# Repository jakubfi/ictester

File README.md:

# Logic IC Tester

Main goal of this project was to make a logic IC tester that allows adding new tests and support for new ICs easily.

## Features

* fully programmable (client-side, in python)
* designed for 5 V TTL logic, but other 5 V logic families can be tested too
* current limiting to 200mA
* current and voltage measurement on VCC and GND pins
* 1.7 μs (<=16-pin ICs) and 2.15 μs (>16-pin ICs) per single logic test cycle
* built-in tests for 4164 and 41256 memories (MARCH C- test in read+write, read/write and page access modes)
* built-in tests for 74121, 74122 and 74123 univibrators
* small and USB powered

## Components

Project is split into three parts:

* [controller](controller) - software for controlling the tester. Look there for command line usage.
* [firmware](fw) - IC tester firmware
* [hardware](hw) - KiCad project files (see also [this pdf](doc/ictester.pdf) for schematic)

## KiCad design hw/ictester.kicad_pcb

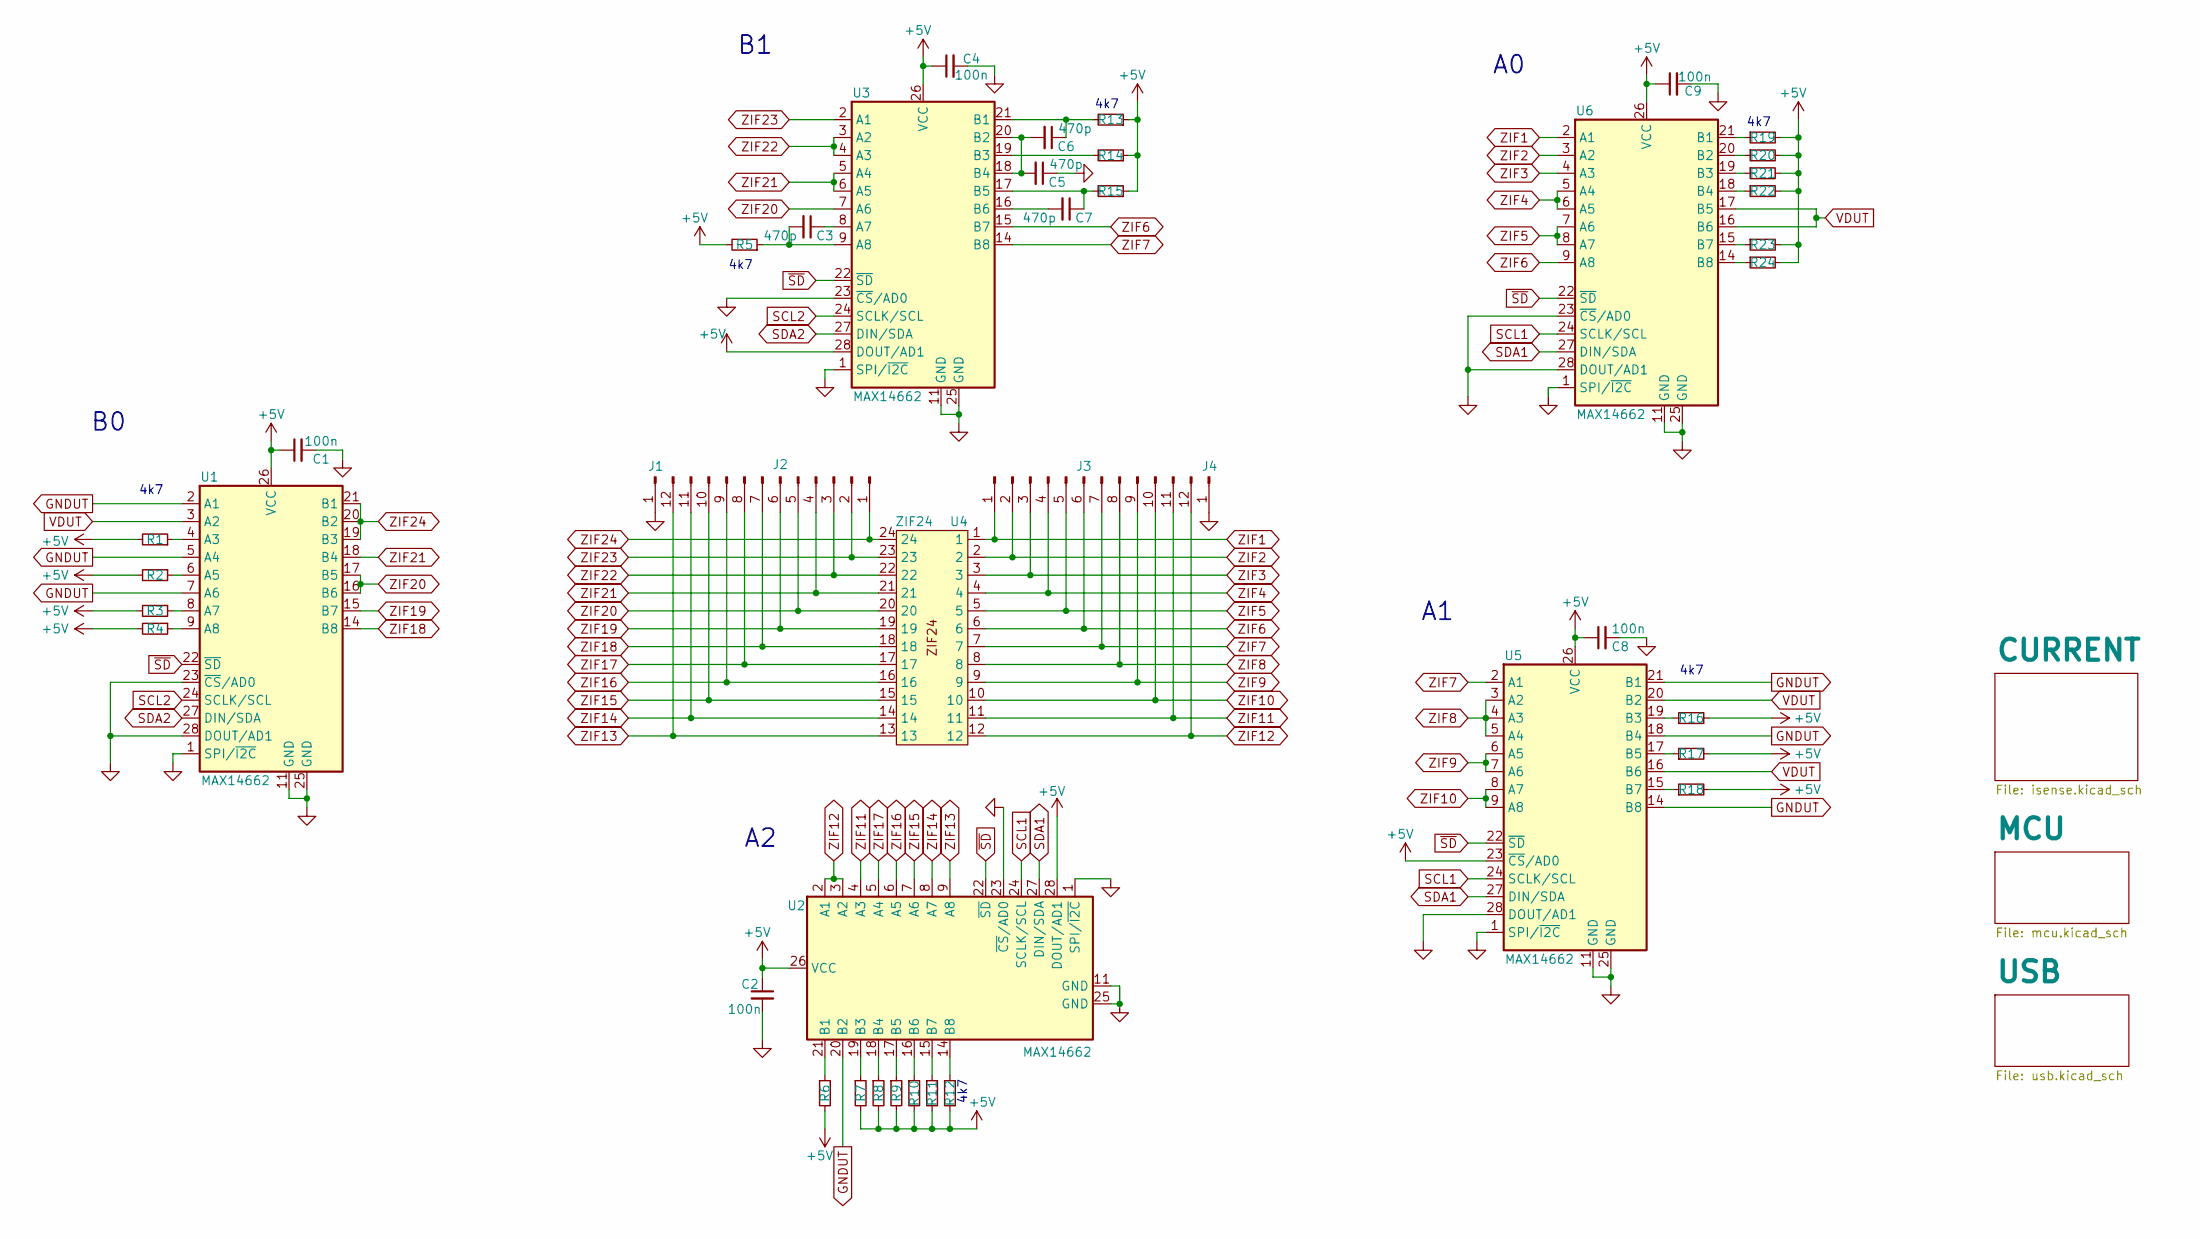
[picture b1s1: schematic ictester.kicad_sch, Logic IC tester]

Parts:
C1, C2, C4, C8, C9: 100n; C_0805_2012Metric_Pad1.18x1.45mm_HandSolder
C3, C5, C6, C7: 470p; C_0805_2012Metric_Pad1.18x1.45mm_HandSolder
J1, J4: Conn_01x01_Pin; PinHeader_1x01_P2.54mm_Vertical
J2, J3: Conn_01x12_Pin; PinHeader_1x12_P2.54mm_Vertical
R1, R2, R3, R4, R5, R6, R7, R8, R9, R10, R11, R12, R13, R14, R15, R16, R17, R18, R19, R20, R21, R22, R23, R24: 4k7; R_0805_2012Metric_Pad1.20x1.40mm_HandSolder
U1, U2, U3, U5, U6: MAX14662; QFN-28-1EP_4x4mm_P0.4mm_EP2.6x2.6mm
U4: ZIF24; DIP_Socket-24_W11.9_W12.7_W15.24_W17.78_W18.5_3M_224-1275-0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

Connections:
+5V: C1.1, C2.1, C4.1, C8.1, C9.1, R1.2, R2.2, R3.2, R4.2, R5.2, R6.2, R7.2, R8.2, R9.2, R10.2, R11.2, R12.2, R13.1, R14.1, R15.1, R16.2, R17.2, R18.2, R19.2, R20.2, R21.2, R22.2, R23.2, R24.2, U1.26 (VCC), U2.26 (VCC), U2.28 (DOUT/AD1), U3.26 (VCC), U3.28 (DOUT/AD1), U5.23 (~CS/AD0), U5.26 (VCC), U6.26 (VCC); also elsewhere on the board
GND: C1.2, C2.2, C4.2, C5.1, C8.2, C9.2, J1.1, J4.1, U1.1 (SPI/~I2C), U1.11 (GND), U1.23 (~CS/AD0), U1.25 (GND), U1.28 (DOUT/AD1), U1.29 (GND), U2.1 (SPI/~I2C), U2.11 (GND), U2.23 (~CS/AD0), U2.25 (GND), U2.29 (GND), U3.1 (SPI/~I2C), U3.11 (GND), U3.23 (~CS/AD0), U3.25 (GND), U3.29 (GND), U5.1 (SPI/~I2C), U5.11 (GND), U5.25 (GND), U5.28 (DOUT/AD1), U5.29 (GND), U6.1 (SPI/~I2C), U6.11 (GND), U6.23 (~CS/AD0), U6.25 (GND), U6.28 (DOUT/AD1), U6.29 (GND); also elsewhere on the board
GNDUT: U1.2 (A1), U1.5 (A4), U1.7 (A6), U2.20 (B2), U5.14 (B8), U5.18 (B4), U5.21 (B1); also elsewhere on the board
unnamed: R1.1, U1.4 (A3)
unnamed: R2.1, U1.6 (A5)
unnamed: R3.1, U1.8 (A7)
unnamed: R4.1, U1.9 (A8)
unnamed: R6.1, U2.21 (B1)
unnamed: R7.1, U2.19 (B3)
unnamed: R8.1, U2.18 (B4)
unnamed: R9.1, U2.17 (B5)
unnamed: R10.1, U2.16 (B6)
unnamed: R11.1, U2.15 (B7)
unnamed: R12.1, U2.14 (B8)
unnamed: C3.1, U3.8 (A7)
unnamed: C3.2, R5.1, U3.9 (A8)
unnamed: C6.1, R13.2, U3.21 (B1)
unnamed: C5.2, C6.2, U3.18 (B4), U3.20 (B2)
unnamed: R14.2, U3.19 (B3)
unnamed: C7.1, R15.2, U3.17 (B5)
unnamed: C7.2, U3.16 (B6)
unnamed: R16.1, U5.19 (B3)
unnamed: R17.1, U5.17 (B5)
unnamed: R18.1, U5.15 (B7)
unnamed: R19.1, U6.21 (B1)
unnamed: R20.1, U6.20 (B2)
unnamed: R21.1, U6.19 (B3)
unnamed: R22.1, U6.18 (B4)
unnamed: R23.1, U6.15 (B7)
unnamed: R24.1, U6.14 (B8)
SCL1: U2.24 (SCLK/SCL), U5.24 (SCLK/SCL), U6.24 (SCLK/SCL); also elsewhere on the board
SCL2: U1.24 (SCLK/SCL), U3.24 (SCLK/SCL); also elsewhere on the board
SDA1: U2.27 (DIN/SDA), U5.27 (DIN/SDA), U6.27 (DIN/SDA); also elsewhere on the board
SDA2: U1.27 (DIN/SDA), U3.27 (DIN/SDA); also elsewhere on the board
VDUT: U1.3 (A2), U5.16 (B6), U5.20 (B2), U6.16 (B6), U6.17 (B5); also elsewhere on the board
ZIF1: J3.1, U4.1, U6.2 (A1); also elsewhere on the board
ZIF2: J3.2, U4.2, U6.3 (A2); also elsewhere on the board
ZIF3: J3.3, U4.3, U6.4 (A3); also elsewhere on the board
ZIF4: J3.4, U4.4, U6.5 (A4), U6.6 (A5); also elsewhere on the board
ZIF5: J3.5, U4.5, U6.7 (A6), U6.8 (A7); also elsewhere on the board
ZIF6: J3.6, U3.15 (B7), U4.6, U6.9 (A8); also elsewhere on the board
ZIF7: J3.7, U3.14 (B8), U4.7, U5.2 (A1); also elsewhere on the board
ZIF8: J3.8, U4.8, U5.3 (A2), U5.4 (A3), U5.5 (A4); also elsewhere on the board
ZIF9: J3.9, U4.9, U5.6 (A5), U5.7 (A6); also elsewhere on the board
ZIF10: J3.10, U4.10, U5.8 (A7), U5.9 (A8); also elsewhere on the board
ZIF11: J3.11, U2.4 (A3), U4.11; also elsewhere on the board
ZIF12: J3.12, U2.2 (A1), U2.3 (A2), U4.12; also elsewhere on the board
ZIF13: J2.12, U2.9 (A8), U4.13; also elsewhere on the board
ZIF14: J2.11, U2.8 (A7), U4.14; also elsewhere on the board
ZIF15: J2.10, U2.7 (A6), U4.15; also elsewhere on the board
ZIF16: J2.9, U2.6 (A5), U4.16; also elsewhere on the board
ZIF17: J2.8, U2.5 (A4), U4.17; also elsewhere on the board
ZIF18: J2.7, U1.14 (B8), U4.18; also elsewhere on the board
ZIF19: J2.6, U1.15 (B7), U4.19; also elsewhere on the board
ZIF20: J2.5, U1.16 (B6), U1.17 (B5), U3.7 (A6), U4.20; also elsewhere on the board
ZIF21: J2.4, U1.18 (B4), U3.5 (A4), U3.6 (A5), U4.21; also elsewhere on the board
ZIF22: J2.3, U3.3 (A2), U3.4 (A3), U4.22; also elsewhere on the board
ZIF23: J2.2, U3.2 (A1), U4.23; also elsewhere on the board
ZIF24: J2.1, U1.19 (B3), U1.20 (B2), U1.21 (B1), U4.24; also elsewhere on the board
~SD: U1.22 (~SD), U2.22 (~SD), U3.22 (~SD), U5.22 (~SD), U6.22 (~SD); also elsewhere on the board

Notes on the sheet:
4k7

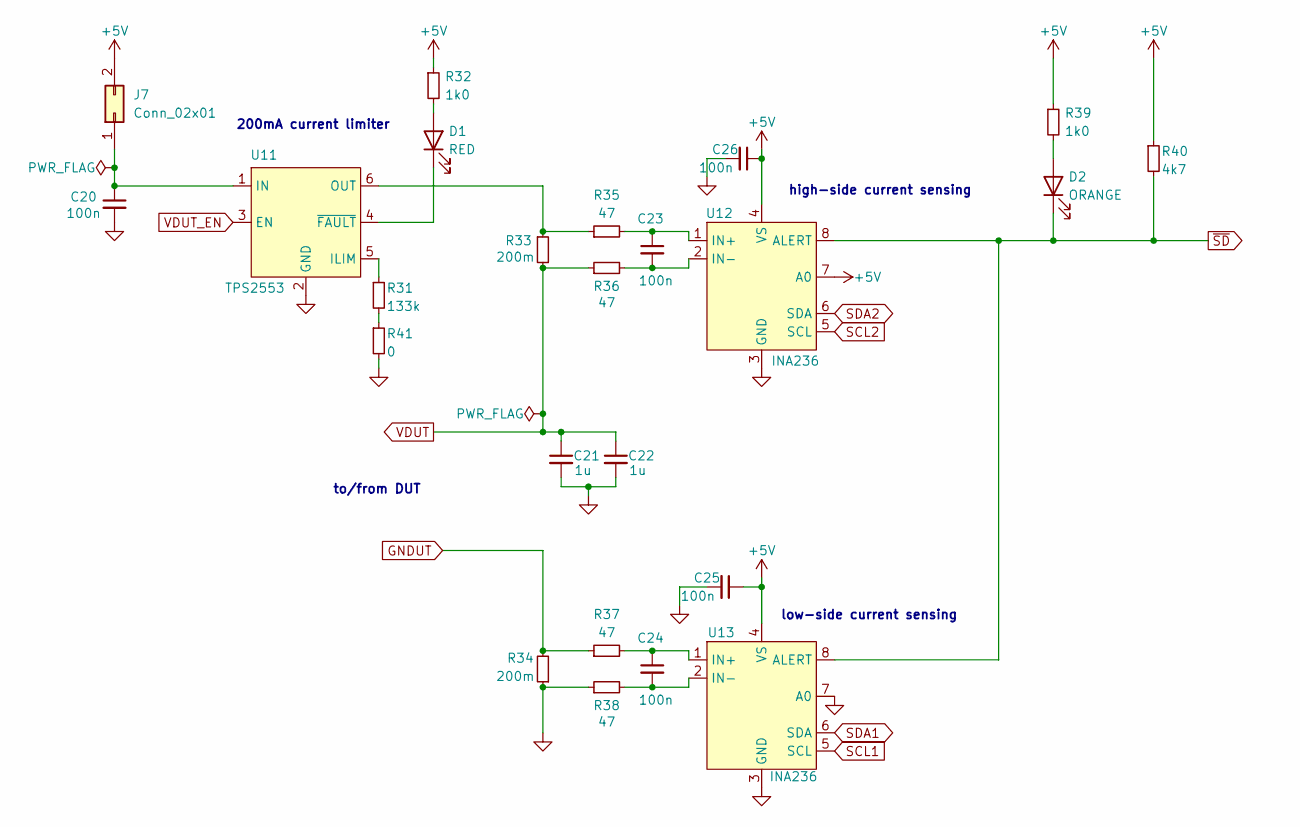
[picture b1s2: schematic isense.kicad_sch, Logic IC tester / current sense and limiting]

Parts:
C20, C23, C24, C25, C26: 100n; C_0805_2012Metric_Pad1.18x1.45mm_HandSolder
C21, C22: 1u; C_0805_2012Metric_Pad1.18x1.45mm_HandSolder
D1: RED; LED_0805_2012Metric_Pad1.15x1.40mm_HandSolder
D2: ORANGE; LED_0805_2012Metric_Pad1.15x1.40mm_HandSolder
J7: Conn_02x01; PinHeader_1x02_P2.54mm_Vertical
R31: 133k; R_0805_2012Metric_Pad1.20x1.40mm_HandSolder
R32, R39: 1k0; R_0805_2012Metric_Pad1.20x1.40mm_HandSolder
R33, R34: 200m; R_0805_2012Metric_Pad1.20x1.40mm_HandSolder
R35, R36, R37, R38: 47; R_0805_2012Metric_Pad1.20x1.40mm_HandSolder
R40: 4k7; R_0805_2012Metric_Pad1.20x1.40mm_HandSolder
R41: 0; R_0805_2012Metric_Pad1.20x1.40mm_HandSolder
U11: TPS2553; SOT-23-6_Handsoldering
U12, U13: INA236; SOT-23-8_Handsoldering

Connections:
+5V: C25.1, C26.1, J7.2, R32.1, R39.1, R40.1, U12.4 (VS), U12.7 (A0), U13.4 (VS); also elsewhere on the board
GND: C20.2, C21.2, C22.2, C25.2, C26.2, R34.1, R38.1, R41.2, U11.2 (GND), U12.3 (GND), U13.3 (GND), U13.7 (A0); also elsewhere on the board
GNDUT: R34.2, R37.1; also elsewhere on the board
unnamed: D1.2 (A), R32.2
unnamed: D1.1 (K), U11.4 (~FAULT)
unnamed: D2.2 (A), R39.2
unnamed: C20.1, J7.1, U11.1 (IN)
unnamed: R31.2, R41.1
unnamed: R31.1, U11.5 (ILIM)
unnamed: R33.1, R35.1, U11.6 (OUT)
unnamed: C23.1, R35.2, U12.1 (IN+)
unnamed: C23.2, R36.2, U12.2 (IN-)
unnamed: C24.1, R37.2, U13.1 (IN+)
unnamed: C24.2, R38.2, U13.2 (IN-)
SCL1: U13.5 (SCL); also elsewhere on the board
SCL2: U12.5 (SCL); also elsewhere on the board
SDA1: U13.6 (SDA); also elsewhere on the board
SDA2: U12.6 (SDA); also elsewhere on the board
VDUT: C21.1, C22.1, R33.2, R36.1; also elsewhere on the board
VDUT_EN: U11.3 (EN); also elsewhere on the board
~SD: D2.1 (K), R40.2, U12.8 (ALERT), U13.8 (ALERT); also elsewhere on the board

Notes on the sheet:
low-side current sensing
200mA current limiter
high-side current sensing
to/from DUT

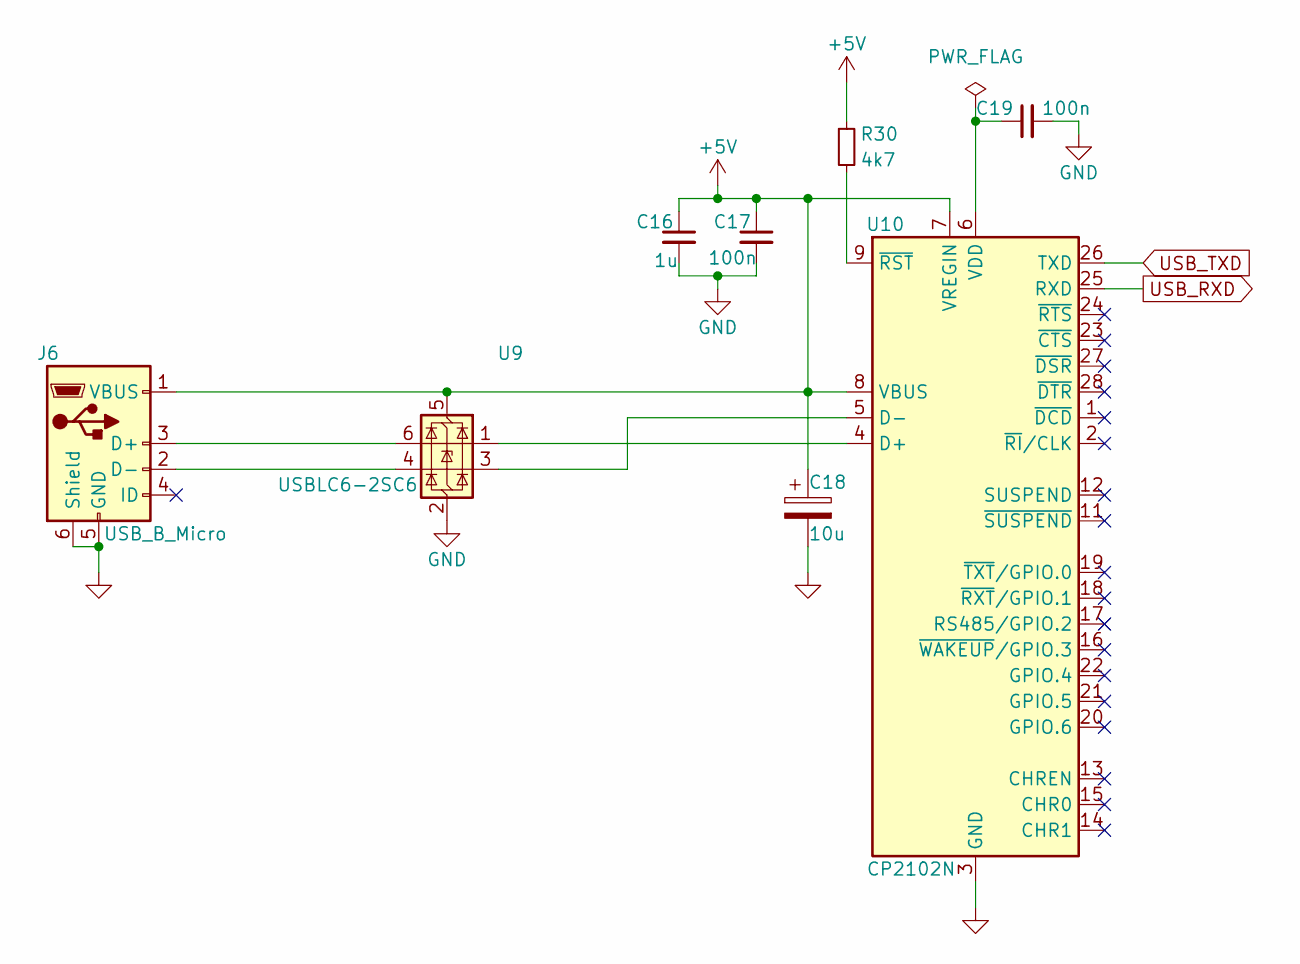
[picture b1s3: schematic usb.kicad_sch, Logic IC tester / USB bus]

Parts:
C16: 1u; C_0805_2012Metric_Pad1.18x1.45mm_HandSolder
C17, C19: 100n; C_0805_2012Metric_Pad1.18x1.45mm_HandSolder
C18: 10u; CP_EIA-3528-21_Kemet-B_Pad1.50x2.35mm_HandSolder
J6: USB_B_Micro; USB_Micro-B_Amphenol_10118193-0001LF_Horizontal
R30: 4k7; R_0805_2012Metric_Pad1.20x1.40mm_HandSolder
U9: USBLC6-2SC6; SOT-23-6
U10: CP2102N; QFN-28-1EP_5x5mm_P0.5mm_EP3.35x3.35mm

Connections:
+5V: C16.1, C17.1, C18.1, J6.1 (VBUS), R30.1, U9.5 (VBUS), U10.7 (VREGIN), U10.8 (VBUS); also elsewhere on the board
GND: C16.2, C17.2, C18.2, C19.2, J6.5 (GND), J6.6 (Shield), U9.2 (GND), U10.3 (GND), U10.29 (GND); also elsewhere on the board
unnamed: J6.3 (D+), U9.6 (I/O1)
unnamed: J6.2 (D-), U9.4 (I/O2)
unnamed: U9.1 (I/O1), U10.4 (D+)
unnamed: U9.3 (I/O2), U10.5 (D-)
unnamed: C19.1, U10.6 (VDD)
unnamed: R30.2, U10.9 (~RST)
USB_RXD: U10.25 (RXD); also elsewhere on the board
USB_TXD: U10.26 (TXD); also elsewhere on the board

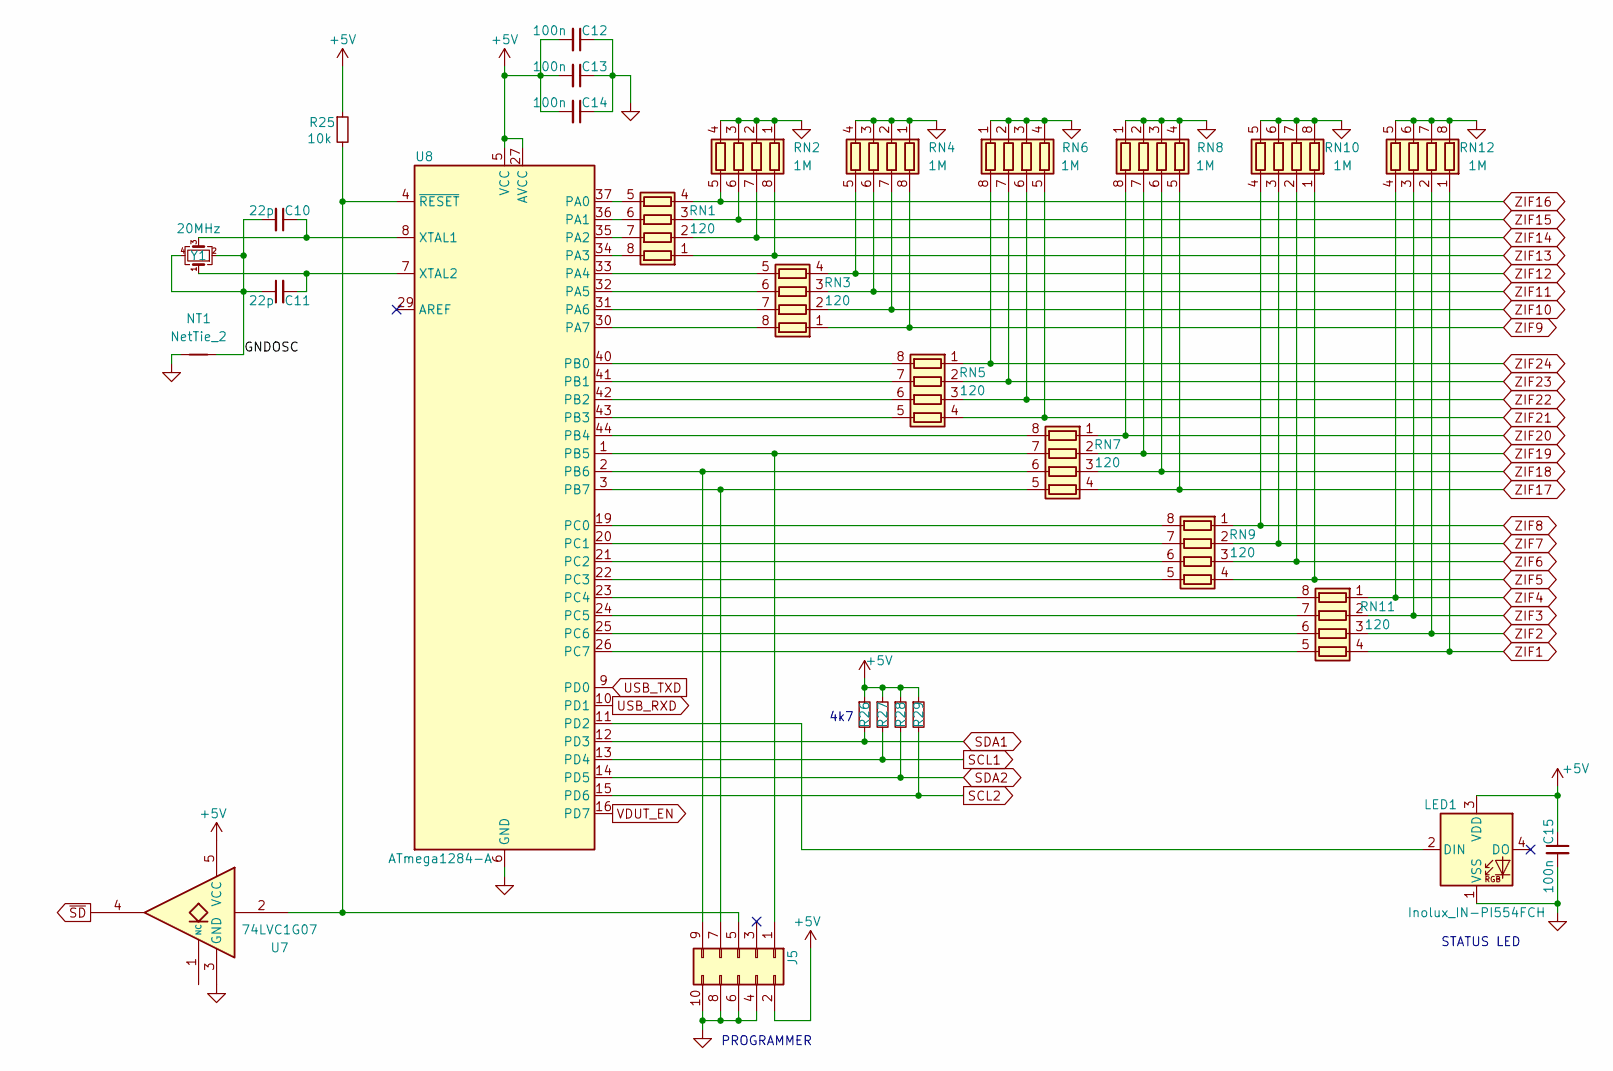
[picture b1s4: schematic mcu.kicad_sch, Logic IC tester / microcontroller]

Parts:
C10, C11: 22p; C_0805_2012Metric_Pad1.18x1.45mm_HandSolder
C12, C13, C14, C15: 100n; C_0805_2012Metric_Pad1.18x1.45mm_HandSolder
J5: Conn_02x05_Odd_Even; PinHeader_2x05_P2.54mm_Vertical
LED1: Inolux_IN-PI554FCH; LED_Inolux_IN-PI554FCH_PLCC4_5.0x5.0mm_P3.2mm
NT1: NetTie_2; NetTie-2_SMD_Pad0.5mm
R25: 10k; R_0805_2012Metric_Pad1.20x1.40mm_HandSolder
R26, R27, R28, R29: 4k7; R_0805_2012Metric_Pad1.20x1.40mm_HandSolder
RN1, RN3, RN5, RN7, RN9, RN11: 120; R_Array_Convex_4x0603
RN2, RN4, RN6, RN8, RN10, RN12: 1M; R_Array_Convex_4x0603
U7: 74LVC1G07; SOT-23-5_HandSoldering
U8: ATmega1284-A; TQFP-44_10x10mm_P0.8mm
Y1: 20MHz; Crystal_SMD_Abracon_ABM3C-4Pin_5.0x3.2mm

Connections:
+5V: C12.2, C13.2, C14.2, C15.1, J5.2, LED1.3 (VDD), R25.1, R26.1, R27.1, R28.1, R29.1, U7.5 (VCC), U8.5 (VCC), U8.17 (VCC), U8.27 (AVCC), U8.38 (VCC); also elsewhere on the board
/MCU/GNDOSC: C10.2, C11.1, NT1.2, Y1.2, Y1.4
GND: C12.1, C13.1, C14.1, C15.2, J5.4, J5.6, J5.8, J5.10, LED1.1 (VSS), NT1.1, RN2.1 (R1.1), RN2.2 (R2.1), RN2.3 (R3.1), RN2.4 (R4.1), RN4.1 (R1.1), RN4.2 (R2.1), RN4.3 (R3.1), RN4.4 (R4.1), RN6.1 (R1.1), RN6.2 (R2.1), RN6.3 (R3.1), RN6.4 (R4.1), RN8.1 (R1.1), RN8.2 (R2.1), RN8.3 (R3.1), RN8.4 (R4.1), RN10.5 (R4.2), RN10.6 (R3.2), RN10.7 (R2.2), RN10.8 (R1.2), RN12.5 (R4.2), RN12.6 (R3.2), RN12.7 (R2.2), RN12.8 (R1.2), U7.3 (GND), U8.6 (GND), U8.18 (GND), U8.28 (GND), U8.39 (GND); also elsewhere on the board
unnamed: J5.1, RN7.7 (R2.2), U8.1 (PB5)
unnamed: J5.5, R25.2, U7.2, U8.4 (~RESET)
unnamed: J5.7, RN7.5 (R4.2), U8.3 (PB7)
unnamed: J5.9, RN7.6 (R3.2), U8.2 (PB6)
unnamed: LED1.2 (DIN), U8.11 (PD2)
unnamed: RN1.8 (R1.2), U8.34 (PA3)
unnamed: RN1.7 (R2.2), U8.35 (PA2)
unnamed: RN1.6 (R3.2), U8.36 (PA1)
unnamed: RN1.5 (R4.2), U8.37 (PA0)
unnamed: RN3.8 (R1.2), U8.30 (PA7)
unnamed: RN3.7 (R2.2), U8.31 (PA6)
unnamed: RN3.6 (R3.2), U8.32 (PA5)
unnamed: RN3.5 (R4.2), U8.33 (PA4)
unnamed: RN5.8 (R1.2), U8.40 (PB0)
unnamed: RN5.7 (R2.2), U8.41 (PB1)
unnamed: RN5.6 (R3.2), U8.42 (PB2)
unnamed: RN5.5 (R4.2), U8.43 (PB3)
unnamed: RN7.8 (R1.2), U8.44 (PB4)
unnamed: RN9.8 (R1.2), U8.19 (PC0)
unnamed: RN9.7 (R2.2), U8.20 (PC1)
unnamed: RN9.6 (R3.2), U8.21 (PC2)
unnamed: RN9.5 (R4.2), U8.22 (PC3)
unnamed: RN11.8 (R1.2), U8.23 (PC4)
unnamed: RN11.7 (R2.2), U8.24 (PC5)
unnamed: RN11.6 (R3.2), U8.25 (PC6)
unnamed: RN11.5 (R4.2), U8.26 (PC7)
unnamed: C10.1, U8.8 (XTAL1), Y1.3
unnamed: C11.2, U8.7 (XTAL2), Y1.1
SCL1: R27.2, U8.13 (PD4); also elsewhere on the board
SCL2: R29.2, U8.15 (PD6); also elsewhere on the board
SDA1: R26.2, U8.12 (PD3); also elsewhere on the board
SDA2: R28.2, U8.14 (PD5); also elsewhere on the board
USB_RXD: U8.10 (PD1); also elsewhere on the board
USB_TXD: U8.9 (PD0); also elsewhere on the board
VDUT_EN: U8.16 (PD7); also elsewhere on the board
ZIF1: RN11.4 (R4.1), RN12.1 (R1.1); also elsewhere on the board
ZIF2: RN11.3 (R3.1), RN12.2 (R2.1); also elsewhere on the board
ZIF3: RN11.2 (R2.1), RN12.3 (R3.1); also elsewhere on the board
ZIF4: RN11.1 (R1.1), RN12.4 (R4.1); also elsewhere on the board
ZIF5: RN9.4 (R4.1), RN10.1 (R1.1); also elsewhere on the board
ZIF6: RN9.3 (R3.1), RN10.2 (R2.1); also elsewhere on the board
ZIF7: RN9.2 (R2.1), RN10.3 (R3.1); also elsewhere on the board
ZIF8: RN9.1 (R1.1), RN10.4 (R4.1); also elsewhere on the board
ZIF9: RN3.1 (R1.1), RN4.8 (R1.2); also elsewhere on the board
ZIF10: RN3.2 (R2.1), RN4.7 (R2.2); also elsewhere on the board
ZIF11: RN3.3 (R3.1), RN4.6 (R3.2); also elsewhere on the board
ZIF12: RN3.4 (R4.1), RN4.5 (R4.2); also elsewhere on the board
ZIF13: RN1.1 (R1.1), RN2.8 (R1.2); also elsewhere on the board
ZIF14: RN1.2 (R2.1), RN2.7 (R2.2); also elsewhere on the board
ZIF15: RN1.3 (R3.1), RN2.6 (R3.2); also elsewhere on the board
ZIF16: RN1.4 (R4.1), RN2.5 (R4.2); also elsewhere on the board
ZIF17: RN7.4 (R4.1), RN8.5 (R4.2); also elsewhere on the board
ZIF18: RN7.3 (R3.1), RN8.6 (R3.2); also elsewhere on the board
ZIF19: RN7.2 (R2.1), RN8.7 (R2.2); also elsewhere on the board
ZIF20: RN7.1 (R1.1), RN8.8 (R1.2); also elsewhere on the board
ZIF21: RN5.4 (R4.1), RN6.5 (R4.2); also elsewhere on the board
ZIF22: RN5.3 (R3.1), RN6.6 (R3.2); also elsewhere on the board
ZIF23: RN5.2 (R2.1), RN6.7 (R2.2); also elsewhere on the board
ZIF24: RN5.1 (R1.1), RN6.8 (R1.2); also elsewhere on the board
~SD: U7.4; also elsewhere on the board

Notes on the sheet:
STATUS LED
PROGRAMMER
4k7

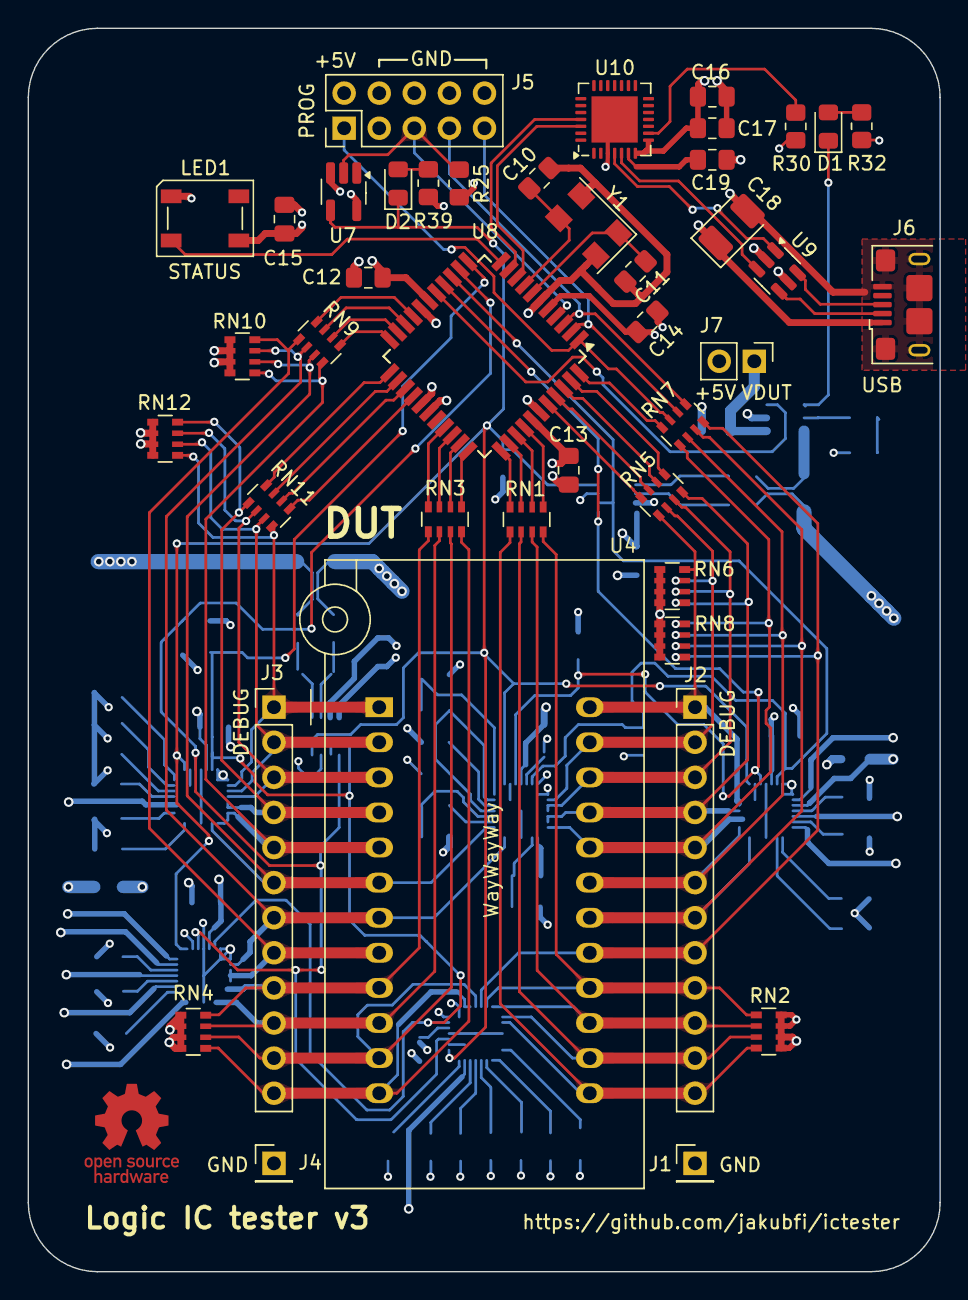
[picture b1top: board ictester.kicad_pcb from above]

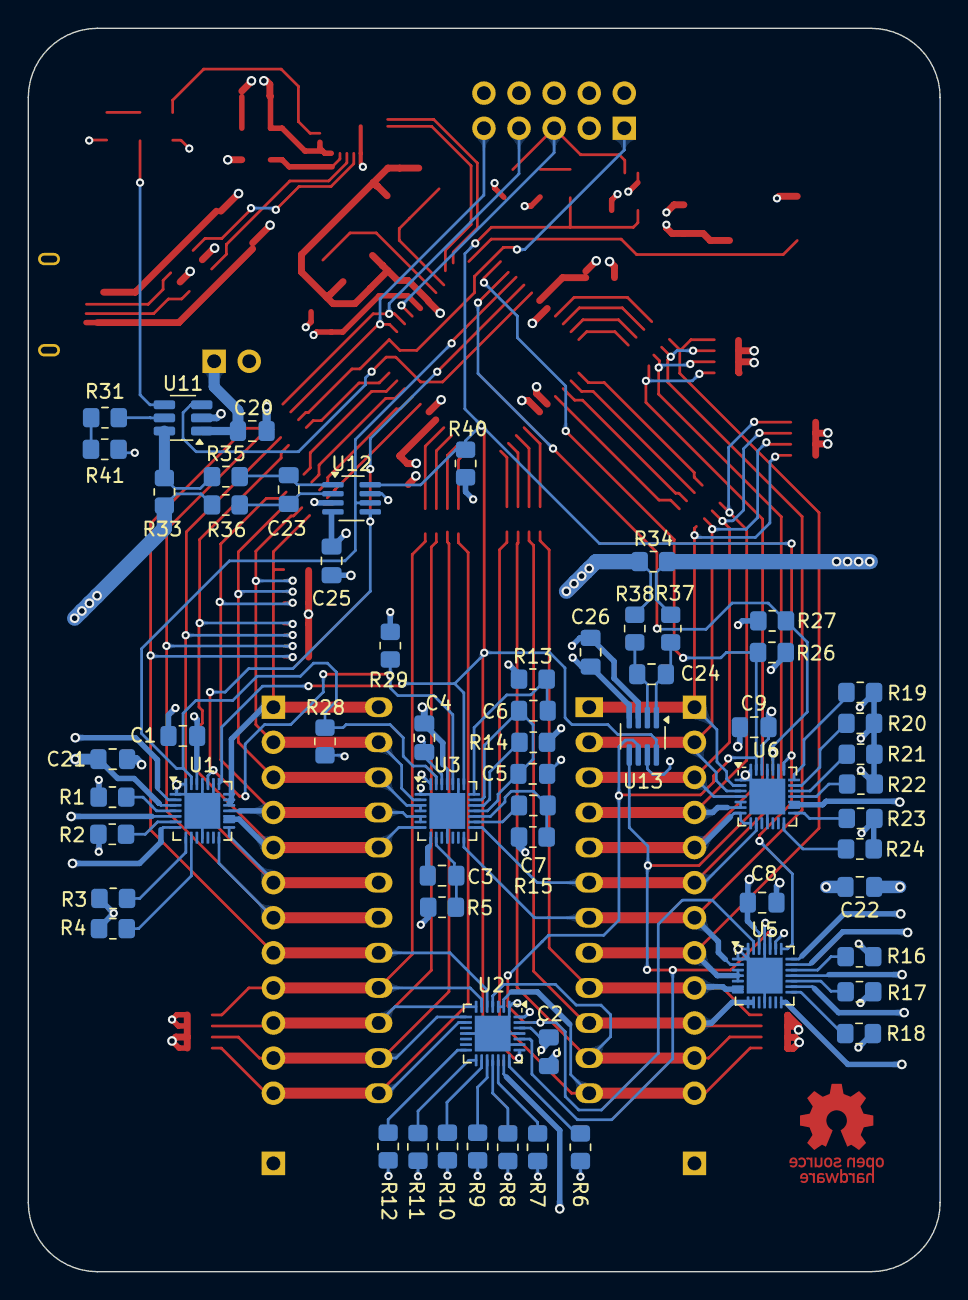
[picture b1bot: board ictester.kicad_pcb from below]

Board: 4 copper layers, 66.0 x 90.0 mm, 104 parts (61 on the bottom side), 109 nets.

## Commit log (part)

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2020-12-15 style fixes, janitorial
2020-12-15 DIP14 map for the final dev-build
2020-12-15 add 7495
2020-12-15 add pin maps for DIP16 and DIP24
2020-12-16 add 74153, selectable maps
2020-12-16 class Test(), deconfigure()
2020-12-16 janitorial
2020-12-16 properly sort 74153
2020-12-16 74181 sketch
2020-12-17 configure/deconfigure pins before/after each test
2020-12-17 bunch of changes
    * add 7430,
    * continue 74181,
    * rename negated pins,
    * Test() class
    * per-test test vectors
    * per-test pin setup
2020-12-17 3kB for a single test
2020-12-18 update tests to use binary_fun_gen()
2020-12-18 go fast
2020-12-18 port speed is defined by the f/w
2020-12-18 nicer output
2020-12-18 74181 - logic vector generator
2020-12-18 formatting
2020-12-18 hide inversion function
2020-12-19 catch duplicate names
2020-12-19 74181, all functions
2020-12-19 74198 sketch
2020-12-19 sort parts numerically
2020-12-20 handle open collector outputs, add 7403
2020-12-20 add 7405, 7406, 7407, 7438
2020-12-24 add 74150
2020-12-29 finally add full 74198 support
2021-05-18 add DIP16 with alternative power, add 7483
2021-05-18 add 7496
2021-05-19 use more binary_fun_gen(), comments, janitorial
2021-05-19 sequentialize() shortcut for SEQ tests
2021-05-19 add 7445
2021-05-19 pylama fixes
2021-05-21 initial 4164 support, working
2021-05-22 test_subtype, more mem tests
2021-05-22 exit with 1 on error, rework loops, per-test loops
2021-05-22 add 74182
2021-05-23 move mem tests to separate source
2021-06-07 add 7411, 74132, 74175, use python3
2021-06-30 add 7440
2021-12-01 add 7453 and 74H53
2021-12-01 fix sorting for 74H and 74S
2022-07-08 add 74174
2022-10-26 rename packages
2022-10-26 add testing A=B output for 181, clarify missing tests
2022-10-27 move bit manipulation methods to Test class
2022-10-28 update package names
2022-10-28 refactor pins, package variants, add sanity checks, fix 7475
2022-11-04 add 74180
2022-11-04 inform about unusual power pins
2022-11-05 add 7472
2022-11-06 add 74125, 74126
2022-11-06 add 74136, 74145
2022-11-06 add 74148
2022-11-06 add 74151
2022-11-06 add 74155, 74156
2022-11-07 add 74157, 74161, 74164
2022-11-28 add 74170
2022-12-08 add 7487
2022-12-08 add 7451
2022-12-08 add 7452
2022-12-08 add 7462
2022-12-08 add 780101
2022-12-08 add 74194
2022-12-08 INPUT -> IN, OUTPUT -> OUT
2022-12-14 add 74S405
2022-12-15 add 7442
2022-12-15 add 74166
2022-12-15 add 7460
2022-12-16 simplify some tests
2022-12-16 code cleanup
2022-12-17 split parts into separate files
2022-12-17 simplify catalog and its printout
2022-12-17 partimport()
2022-12-18 simplity 74145
2022-12-18 case-insensitive part name matching
2022-12-18 extend 7487 tests
2022-12-18 eimplify/extend 74150, 74151
2022-12-18 simplify 74153
2022-12-18 simplify 74154
2022-12-18 simplify 74155
2022-12-18 simplify 74157
2022-12-18 nicer 74180
2023-02-25 add 74h106
2023-03-31 more robust 74170
2023-04-06 add 7461
2023-04-06 renames to match existing "minimal" chip variations
2023-04-18 add 7485
2023-04-18 add 74193
2023-04-19 500us startup delay
2023-04-26 Add listing tests for each part
2023-04-28 update/fix 7490
2023-04-29 Makefile programmer fixes
2023-04-29 add time measurement
2023-04-29 4164: MARCH C- tests
2023-04-30 add total test time measurement
2023-04-30 74x tester go 2x faster
    * remove _NOP();
    * unroll loops
    * read/write ports directly
2023-04-30 mem: cleanups, comments
2023-04-30 74182: wrong test type, COMB instead of SEQ
2023-04-30 74s405: wrong test type, COMB instead of SEQ
2023-04-30 comments
2023-05-04 output formatting, naming
2023-05-12 remove unused struct field
2023-05-13 go faster
2023-05-13 comment
2023-05-31 add 41256, rework march c- test
2023-05-31 sort by families in --list
2023-06-17 cleanup unused
2023-06-25 add 74LS54
2023-06-25 add 7414
2023-06-25 add 74109
2023-06-25 add 74112
2023-06-28 introduce BinaryVector, we'll see how it goes
2023-06-28 add 9312
2023-06-28 150, 151: better inhibit test
2023-06-28 better debug
2023-06-28 todo update
2023-06-28 better BV stringization
2023-06-28 small BV optimizations
2023-06-29 fix listing LS chips
2023-06-30 allow Test.body to be a callable
2023-06-30 use BV everywhere
2023-06-30 lazy load heaviest test bodies
2023-07-01 move time measurement inside test run
2023-07-01 fix 74181 test
2023-07-01 use lower-case file names
2023-07-02 only open serial when needed
2023-07-02 use BV even more
2023-07-02 add MCU reset to Makefile
2023-07-03 Make the H/W responsible for pin mapping. Also:
    * --serial_debug is now --debug-serial
    * remove total time measurement (makes no sense)
    * update protocol to be closer to the final one
    * clean up prototypes (properties, package naming, etc.)
2023-07-03 BV byte conversion, Tester.send bytes, debug fixes
2023-07-03 ups, OC is also an output
2023-07-03 move const structs to flash, cleanup socket guessing
2023-07-03 add protocol constants
2023-07-03 hide body manipulation inside Test
2023-07-03 separate qc
2023-07-04 separate Transport
2023-07-04 introduce test params
2023-07-04 use loops instead of loops power
2023-07-05 update error codes
2023-07-06 add kicad files
2023-07-06 protocol doc update
2023-07-06 separate protocol header
2023-07-06 rename variables and constants
2023-07-08 initial logic.c split
2023-07-08 use LTO
2023-07-08 no objdump when displaying stats
2023-07-09 add ERR_PIN_COMB error
2023-07-09 h/w update
2023-07-21 hw update
2023-07-23 example of simple body for 7400
2023-07-24 74181: separate A==B test
2023-08-06 fix 7460, 74h62
2023-08-06 7460: increase loops
2023-08-06 Initial version for the new H/W. Also fix 74H106.
2023-08-06 41x DRAM tests adjusted for the new H/W
2023-08-06 calculate zif_pin once
2023-08-06 speed: separate logic tests for 2- and 3-port ICs
2023-08-06 rename LICENSE.txt file
2023-08-06 dim the lights
2023-08-07 fix test result handling
2023-08-08 draft: redefine dut connect/disconnect
2023-08-08 change perspective on DUT pins
2023-08-08 separate dut_connect/_disconnect
2023-08-11 univibrator tests, initial, working
2023-08-11 use _BV macro
2023-08-12 remove dangling whitespaces
2023-08-21 fix 7450
2023-08-23 readme
2023-08-25 fix LED status, more sane result handling
2023-08-30 fix 7472
2023-08-30 add 7416
2023-08-30 add 7401
2023-08-30 add 7409
2023-08-30 add 7476
2023-09-01 protocol update
2023-09-01 doc: endianness
2023-09-02 late connect, early disconnect, skip after fail
2023-09-02 optional DUT read delay
2023-09-02 more readable send_*() transport methods
2023-09-02 move run handling into handle_run()
2023-09-03 read delay is a test param
2023-09-03 simplify handle_run()
2023-09-03 SEQ and COMB are now LOGIC
    * make SEQ and COMB tests into LOGIC tests
    * allow None as output in vector definition (i.e. vector not checked)
    * vectors with '+' or '-' bit values are expanded to 2-vectors
    * send "skip vector check" flag as VCC bit in the vector
    * simplify Test.body/Test.vectors situation
    * fw: store "skip check" separately for each vector and use it to make
2023-09-03 add delays for 780101 and 7489
2023-09-03 fix h52, h53, 53, 156, update todo
2023-09-04 show "no check" vectors in debug output
2023-09-04 fix 74166
2023-09-05 additional delays for 240 and 244
2023-09-05 add 74ls51
2023-09-05 74123 rework
    * drop .trig_loops, use constant RETRIG_LOOPS
    * add .val_clear_trig, add test for triggering with rising CLR
    * fix issue witn 74hct123 sensitive to non-trigger changes (unwanted CLR trigger case)
    * cleanup trigger and output check functions
    * fix output checking
    * add comments
2023-09-07 fix 74ls51, update 240/244, add 74ls365, todo update
2023-09-09 dut vs mcu perspective renames, janitorial
2023-09-09 separate sw.[ch]
2023-09-09 no strict prototypes, janitorial
2023-09-10 pin masking - naming changes
2023-09-10 protocol: better test parameters handling
2023-09-10 Device autodetection
2023-09-10 protocol: allow for multiple DUT setups
2023-09-11 fw-side support for multiple (2 for now) DUT configs
2023-09-12 bump max configs to 4
2023-09-12 sw support for multiple configs
2023-09-12 add 74s245
2023-09-12 BV go faster
2023-09-12 delay for 7401
2023-09-12 re-add missed HiZ
2023-09-12 fix 7427
2023-09-12 BV.vand() and BV.vor() reduce to a single bool
2023-09-12 make more tests full coverage
2023-09-13 update 74125
2023-09-13 faster logic test loop
2023-09-13 nicer stats
2023-09-14 use 1s and 0s in debug output for vectors
2023-09-14 fix inputs order
2023-09-14 no spaces in signal names
2023-09-14 report the failed vector
2023-09-15 name matching + main() janitorial
    * IC with a similar name is suggested when no exact match found
    * separate some main() functions
    * open serial port late
    * handle serial port open errors
    * cleanups, renames
2023-09-15 oops.
2023-09-15 make led.c more sane
2023-09-15 int/uint cleanup
2023-09-16 dram test: honor weak pullups
2023-09-16 Allow for easy DRAM speed testing (CAS-Dout delay)
2023-09-16 allow selecting a specific test to run
2023-09-16 honor weak pullups in univib tests. todo update.
2023-09-17 janitorial, remove unused
2023-09-17 Towards The Protocol
    * part can represent itself "the protocol way"
    * more enums
2023-09-17 Towards The Protocol part II
    * TestType is an enum
    * class hierarchy for Test
    * Tests can now represent themselves "the protocol way"
    * parameters are now done in Test* classes (especially delay is
    now calculated in one place)
    * TestVector can now represent itself
2023-09-17 Towards The Protocol part III
    * pin usage data required for LOGIC tests only
    * inputs/outputs are not required for dram and univibs anymore
    * MAX_PARAMS is now 2
    * more Enums (dram and univib)
    * dram test constructor args order fix
    * protocol doc update
2023-09-18 logging
    * use logging instead of hand-crafted debug
    * --verbose instead of --debug*
    * add short versions of cmdline options
    * simplify transport verbose output
2023-09-18 rework main loop a bit
2023-09-20 fix TestDRAM arg order
2023-09-21 The Protocol part I
    * framing for command side of the protocol, protocol structs
    * *_test_setup() - test specific setups
    * test parameters are now test-specific
    * pin masking is now specific to LOGIC tests
    * cfgnum handled with a pointer to config internally + zif_config_select()
    * vectors can be loaded by chunks
2023-09-24 The Protocol part II
    * framing for the response side of the protocol; structs
    * minimal handling of framed responses on SW side, needs more work
    * *_store_result() on test side of processing
    * handling failure details for mem test
2023-09-24 The Protocol part III
    * DUT and Test related commands moved to Part and Test
    * move test result decoding to Test
    * drop Tester class alltogether
    * read delay available for all tests (but test may ignore it)
    * elapsed time measured by the test, test result stats done in
    ictester.py
2023-09-24 split prototypes.py
2023-09-24 more log levels
2023-09-26 s/mem/dram/g and some other naming fixes
2023-09-28 fix typos
2023-09-28 fix disconnection issue
2024-06-16 don't disconnect NULL configurations
2024-06-22 report failing loop number
2024-07-03 7403 timings
2024-11-30 fix qc
2024-11-30 fix parts listing with short switches
2024-11-30 get rid of partimport()
2024-12-01 readme update
2024-12-02 use colorama
2025-02-02 make fw _almost_ port-mapping-agnostic
2025-02-02 .gitignore update, dram.c comments
2025-02-02 reorder ZIF ports (cosmetic only)
2025-02-03 cosmetic
2025-02-14 add 7454
2025-02-14 add 74368
2025-04-12 v3 compatibility, contd.
2025-04-16 H/W v3
2025-04-16 update schematic
2025-04-16 readme/doc update
2025-04-20 fix 7473
2025-04-20 fix 7476
2025-04-20 fix 7496
2025-04-20 fix 7475
2025-04-20 update 74125, 74126
2025-04-20 add/update 74365, 74366, 74367, 74368
2025-04-20 name fix
2025-04-21 add 7492, update 7493
2025-04-21 add 74165
2025-04-21 add 74173
2025-04-21 add 74169
2025-04-22 improve oscillator grounding
2025-04-22 add 74190, 74191
2025-04-23 add 74138
2025-04-26 generalize current statistics
2025-04-26 minimal current measurement for univibs
2025-04-30 Specify INA236A, add note about INA236A/B variants
